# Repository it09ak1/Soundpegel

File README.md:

Soundpegel
==========

microcontroller abschlussprojekt

Bauteile: 
  - ATmega16
  -	Atmel AVR Board
  -	Verstärker
  -	Mikrofon
  -	Brückengleichrichter

Programmfunktionen:
  -	Ausgabe der Stimmenlautstärke
  -	Ausgabe des Bass

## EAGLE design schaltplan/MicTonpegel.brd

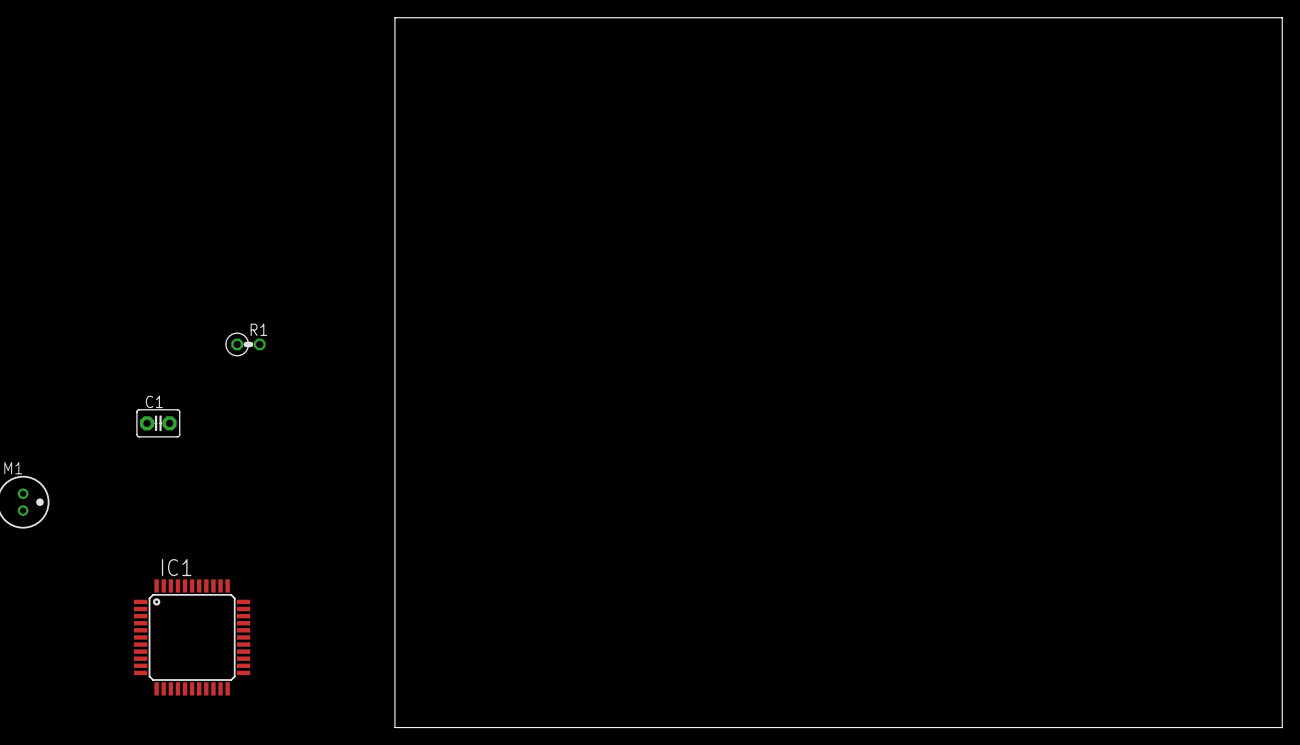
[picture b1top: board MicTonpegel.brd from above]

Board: 2 copper layers, 100.0 x 80.0 mm, 4 parts (0 on the bottom side), 4 nets, no tracks yet.

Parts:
C1: 0,1µF; C2.5-3
IC1: MEGA16-A; TQFP44
M1: ELECTRET_MICROPHON-F6035AP; F6035AP
R1: 2,2k; 0207/2V

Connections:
GND: IC1.6, IC1.28, M1.2
unnamed: IC1.5, R1.2
unnamed: C1.1, M1.1, R1.1
unnamed: C1.2, IC1.37

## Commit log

2012-07-20 add Folder: schaltCode and schaltplan with all fildes.
2012-07-24 The user can speak in the mic and the result is shown on the Atmel board, but not perfect.
2012-07-28 key function now possible: program 1: breath barometers, program 2: max breath, program 0: delete values. Programs works.
2012-07-29 add new function: average
2012-07-30 Changed to actual wiring
2012-07-30 add a new program: program 3: Counter if a max value is achieved. Change the average calculation from 8 to 30 values.
2012-08-02 Final Version 1.0
